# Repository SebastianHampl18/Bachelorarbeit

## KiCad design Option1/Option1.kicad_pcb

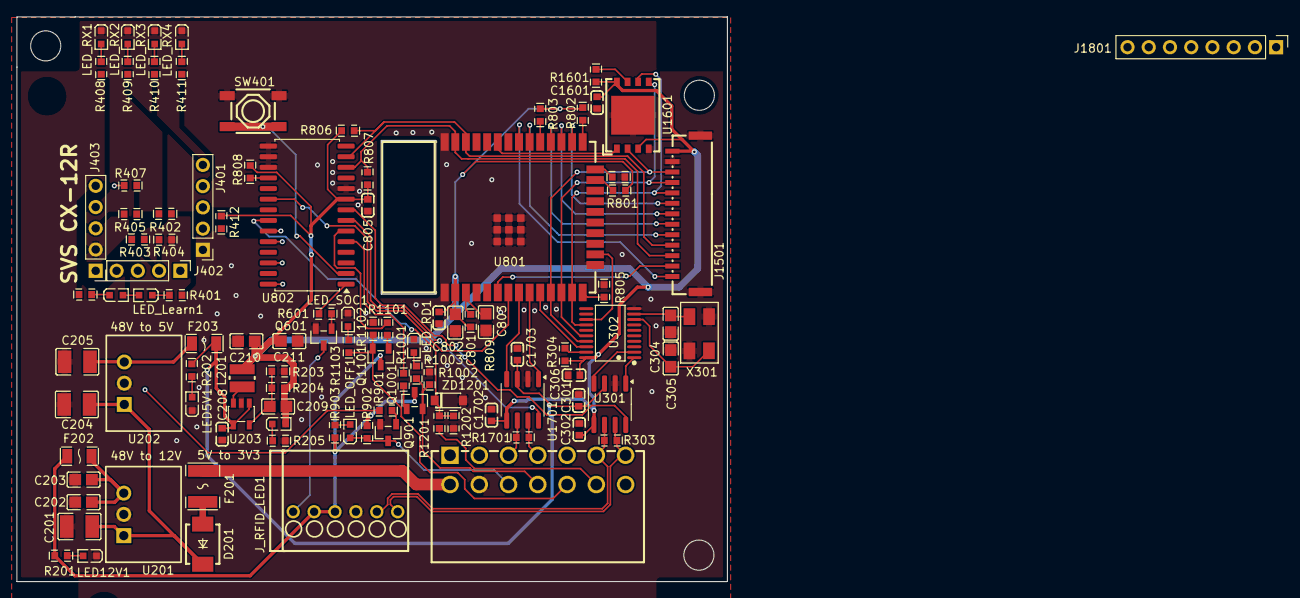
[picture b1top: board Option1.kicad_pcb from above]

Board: 2 copper layers, 85.0 x 67.5 mm, 104 parts (0 on the bottom side), 83 nets.

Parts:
C201, C204: 10uF / 63V; C1210
C202, C203: 10uF / 16V; C0805
C205: 22uF / 10V; C1210
C208: 22uF / 6.3V; C0603
C209, C304, C305: 22pF; C0805
C210, C211, C801: 22uF; C0805
C301, C302, C306, C802, C805, C1601, C1702, C1703: 100nF; C0603
C803: 10 uF; C0805
D201: SS310_C14281; SMB_L4.6-W3.6-LS5.3-R-RD
F201: JK-MSMD030-60V; F1812
F202: JK-NSMD075-13.2; F1206
F203: JK-NSMD075; F1206
J401, J403: Conn_01x05_Pin; PinHeader_1x05_P2.54mm_Vertical
J402: Conn_01x04_Pin; PinHeader_1x04_P2.54mm_Vertical
J503: KF2EDGKRG-3.5-2*7P; CONN-TH_14P-P3.50_KEFA_KF2EDGKRG-3.5-2X7P
J999: Phoenix_Connetor_07x2pin_toWire; Phonix_Connector_07x2pin_toWire
J1501: GH-13AB; CONN-SMD_GH-13AB
J1801: Conn_01x08_Socket; PinHeader_1x08_P2.54mm_Vertical
J_RFID_LED1: 1989780; CONN-TH_6P-P2.50_1989780
L201: 2.2uH; IND-SMD_L3.0-W3.0_NR3010
LED3V3: XL-1608SYGC-06; LED0603-RD_GREEN
LED5V1: XL-1608SYGC-5; LED0603-RD_GREEN
LED12V1: XL-1608SYGC-12; LED0603-RD_GREEN
LED_Error1: XL-1608SYGC-06; LED0603-RD_GREEN
LED_Learn1: XL-1608SYGC-06; LED0603-RD_GREEN
LED_OFF1: XL-1608SYGC-06; LED0603-RD_GREEN
LED_RD1: XL-1608SYGC-06; LED0603-RD_GREEN
LED_RX1, LED_RX2, LED_RX3, LED_RX4: XL-1608SYGC-06; LED0603-RD_GREEN
LED_SOC1: XL-1608SYGC-06; LED0603-RD_GREEN
Q601, Q901, Q1001, Q1101: JY2302; SOT-23-3_L2.9-W1.3-P0.95-LS2.4-BR
R201, R903, R1003, R1103: 1.8kΩ; R0603
R202: 560Ω; R0603
R203: 150k; R0603
R204: 680k; R0603
R205, R401, R406, R408, R409, R410, R411: 220Ω; R0603
R303, R1701: 120Ω; R0603
R304, R801, R802, R803, R804, R805, R808: 10kΩ; R0603
R402, R407: 10K; R0603
R403, R404, R405, R412, R809, R902, R1002, R1102, R1202, R1601: 10k; R0603
R601, R901, R1001, R1101: 1k; R0603
R806, R807: 4.7kΩ; R0603
R1201: 27k; R0603
SW401: 4*4*1.7; SW-SMD_4P-L5.2-W5.2-P3.70-LS6.5
U201: U7812-500; PWRM-TH_3P-L11.6-W9.0-P2.54
U202: U7805-500; PWRM-TH_3P-L11.6-W9.0-P2.54
U203: SY8089AAAC; SOT-23-5_L3.0-W1.7-P0.95-LS2.8-BR
U301, U1701: TJA1051T-3; SOIC-8_3.9x4.9mm_P1.27mm
U302: MCP2515-I/ST; TSSOP-20_L6.5-W4.4-P0.65-LS6.4-BL
U801: ESP32-WROOM-32E-N4; WIFI-SMD_ESP32-WROOM-32E-A
U802: MCP23017_SO; SOIC-28W_7.5x17.9mm_P1.27mm
U1601: W25Q512JVEIQ; WSON-8_L8.0-W6.0-P1.27-TL-EP
X301: XL1EL89CSI-111YLC-8M; CRYSTAL-SMD_4P-L5.0-W3.2-BL-7I12288F20UCG
ZD1201: BZT52C3V6_C2113; SOD-123_L2.8-W1.8-LS3.7-RD

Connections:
3.3V: C209.1, C210.1, C211.1, C302.1, C306.1, C801.1, C802.1, C805.1, C1601.2, C1702.1, J403.1, J1501.13, J1801.8, L201.2, LED3V3.2 (A), LED_Error1.2 (A), LED_Learn1.2 (A), R204.1, R304.2, R402.2, R403.2, R405.2, R407.2, R412.1, R801.1, R802.1, R803.1, R806.2, R807.2, R808.2, R809.1, R1601.2, U301.5 (VIO), U302.20 (VDD), U801.2 (3V3), U802.9 (VDD), U1601.3 (WP#(IO2), U1601.8 (VCC), U1701.5 (VIO)
5V: C208.1, C301.1, C1703.1, F203.2, R202.2, U203.1 (EN), U203.4 (IN), U301.3 (VCC), U1701.3 (VCC)
12V: F202.2, J_RFID_LED1.2, J_RFID_LED1.3, Q1001.3 (D), Q1101.3 (D), R201.2, R902.2, R903.2
48V: F201.1, J503.2
48V_Fused: C201.1, C204.1, D201.2 (K), U201.1 (Vin), U202.1 (Vin)
/CAN1 Tranciever/CAN_H: J503.7, R1701.2, U1701.7 (CANH)
/CAN1 Tranciever/CAN_L: J503.5, R1701.1, U1701.6 (CANL)
/CAN1 Tranciever/CAN_S-Mode: U802.7 (GPB6), U1701.8 (S)
/CAN2_Tranciever/CAN_H: J503.13, J_RFID_LED1.6, R303.2, U301.7 (CANH)
/CAN2_Tranciever/CAN_L: J503.11, J_RFID_LED1.5, R303.1, U301.6 (CANL)
/CAN2_Tranciever/CAN_RX: U301.4 (RXD), U302.2 (RXCAN)
/CAN2_Tranciever/CAN_S-Mode: U301.8 (S), U802.8 (GPB7)
/CAN2_Tranciever/CAN_TX: U301.1 (TXD), U302.1 (TXCAN)
/MCT Wlan/ESP_EN: C803.2, R809.2, U801.3 (EN)
/MCT Wlan/LED_On: R601.2, U802.1 (GPB0)
/MCT Wlan/LED_Signal: R1201.1, R1202.2, U802.22 (GPA1), ZD1201.1 (K)
/MCT Wlan/SPI_CS_RFID: J1801.1, U802.3 (GPB2)
/MCT Wlan/SPI_RST_RFID: J1801.7, U802.4 (GPB3)
/MCT Wlan/TX_2 (Remote Drive): R1001.2, U802.5 (GPB4)
/MCT Wlan/TX_3 (SOC): R1101.2, U802.6 (GPB5)
/Notaus Schalter/Notaus_VCU: J503.6, LED_OFF1.1 (K), Q901.3 (D), R902.1
/Powersupply/12V_OUT: C202.1, C203.1, F202.1, U201.3 (Vout)
/RemoteDrive Schalter/RemoteDrive_VCU: J503.8, Q1001.2 (S), R1002.2, R1003.2
/SOC Schalter/SOC_VCU: J503.10, Q1101.2 (S), R1102.2, R1103.2
/Stecker Input/VCU_LED: J503.12, R1201.2
/Stecker LED - RFID/Status_LED -: J_RFID_LED1.1, Q601.3 (D)
F2_Sel: J402.2, R403.1, R404.1
Fehler_LED: J403.5, R406.1, R407.1, U802.23 (GPA2)
GND: C201.2, C202.2, C203.2, C204.2, C205.2, C208.2, C210.2, C211.2, C301.2, C302.2, C304.1, C305.1, C306.2, C801.2, C802.2, C803.1, C805.2, C1601.1, C1702.2, C1703.2, J401.1, J403.2, J503.4, J1501.12, J1501.14, J1501.15, J1801.6, J_RFID_LED1.4, LED5V1.1 (K), LED12V1.1 (K), LED_RD1.1 (K), LED_RX1.1 (K), LED_RX2.1 (K), LED_RX3.1 (K), LED_RX4.1 (K), LED_SOC1.1 (K), Q601.2 (S), Q901.2 (S), R203.2, R205.2, R404.2, R804.2, R805.2, R1002.1, R1102.1, R1202.1, SW401.3, SW401.4, U201.2 (GND), U202.2 (GND), U203.2 (GND), U301.2 (GND), U302.10 (VSS), U801.1 (GND), U801.15 (GND), U801.38 (GND), U801.39 (GND), U802.10 (VSS), U802.15 (A0), U802.16 (A1), U802.17 (A2), U1601.4 (GND), U1601.9 (EP), U1701.2 (GND), X301.2 (GND), X301.4 (GND), ZD1201.2 (A)
IO0: R802.2, U801.25 (IO0)
IO2: R804.1, U801.24 (IO2)
IO4: J1501.8, U801.26 (IO4)
IO5: R803.2, U801.29 (IO5)
IO13: U302.13 (~INT), U801.16 (IO13)
IO14: J1501.9, J1801.2, U302.14 (SCK), U801.13 (IO14), U1601.6 (CLK)
IO16: J1501.7, U801.27 (IO16)
IO17: J1501.6, U801.28 (IO17)
IO18: J1501.5, U801.30 (IO18)
IO19: J1501.1, U801.31 (IO19)
IO21: U801.33 (IO21), U1601.1 (~CS)
IO22: J1501.4, R806.1, U801.36 (IO22), U802.13 (SDA)
IO23: J1501.3, R807.1, U801.37 (IO23), U802.12 (SCK)
IO25: U302.18 (~CS), U801.10 (IO25)
IO26: J1501.11, J1801.4, U302.17 (SO), U801.11 (IO26), U1601.2 (DO(IO1))
IO27: J1501.10, J1801.3, U302.16 (SI), U801.12 (IO27), U1601.5 (DI(IO0))
IO32: U801.8 (IO32), U1701.4 (RXD)
IO33: U801.9 (IO33), U1701.1 (TXD)
IO34: J1501.2, U801.6 (IO34)
IO35: U801.7 (IO35), U802.20 (INTA)
LED_Modus: J401.3, R401.1, R402.1, U802.21 (GPA0)
Lernmodus: J401.2, R412.2, SW401.1, SW401.2, U802.2 (GPB1)
MTD0: R801.2, U801.23 (IO15)
MTD1: R805.1, U801.14 (IO12)
unnamed: D201.1 (A), F201.2
unnamed: LED3V3.1 (K), R205.1
unnamed: LED5V1.2 (A), R202.1
unnamed: LED12V1.2 (A), R201.1
unnamed: LED_Error1.1 (K), R406.2
unnamed: LED_Learn1.1 (K), R401.2
unnamed: LED_OFF1.2 (A), R903.1
unnamed: LED_RD1.2 (A), R1003.1
unnamed: LED_RX1.2 (A), R408.2
unnamed: LED_RX2.2 (A), R409.2
unnamed: LED_RX3.2 (A), R410.2
unnamed: LED_RX4.2 (A), R411.2
unnamed: LED_SOC1.2 (A), R1103.1
unnamed: Q601.1 (G), R601.1
unnamed: Q901.1 (G), R901.1
unnamed: Q1001.1 (G), R1001.1
unnamed: Q1101.1 (G), R1101.1
unnamed: C205.1, F203.1, U202.3 (Vout)
unnamed: C209.2, R203.1, R204.2, U203.5 (FB)
unnamed: L201.1, U203.3 (LX)
unnamed: C304.2, U302.9 (OSC1), X301.3
unnamed: C305.2, U302.8 (OSC2), X301.1
unnamed: R304.1, U302.19 (~RESET)
unnamed: R808.1, U802.18 (~RESET)
unnamed: R1601.1, U1601.7 (~HOLD/RESET#(IO3))
RX_1: J402.4, R408.1, R901.2
RX_2: J402.3, R409.1, U802.24 (GPA3)
RX_3: J401.5, R410.1, U802.26 (GPA5)
RX_4: J401.4, R411.1, U802.28 (GPA7)
TX_Analog: J403.3, R405.1

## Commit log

2025-05-28 Stand mit annähernd fertigem Schaltplan, Flashen, SPIFlash, Display, MCT Beschaltung fehlen;Datenbläter, etc
2025-05-30 SPI Flash hinzugefügt, IN/Outputs vereinheitlicht, USB Flash Möglichkeit hinzugefügt, Display fehtl noch
2025-06-03 Added Export for Review 1
2025-06-13 USB auf 3V3 umgebaut
2025-06-19 Erste issues eingearbeitet
2025-06-19 Datenblätter für korrigierten SPI-Flash und CAN2 Controller Oszillator hinzugefügt
2025-06-19 Oszillator für CAN-Controller hinzugefügt, Abschlusswiderstände eingefügt
2025-06-19 Transitor getauscht, Pulldown Widerstände für Definierten LOW Pegel hinzugefügt
2025-06-19 Widerstandswerte des Spannungsteiler angepasst und korrigiert
2025-06-19 Zweite 3V3 Spannungsversorgung für Display hinzugefügt
2025-06-19 SPI Flash getauscht
2025-06-19 Pojekt und Backups
2025-06-19 Alte Stecker zum litzen verschrauben auf Platine vorgesehn, 14 Pin Stecker zum Stecken fehlt, RFID und LED abklären
2025-06-23 USB Schaltung angepasst, Transistoren korrigiert, Stecker ausgetauscht, Dioden hinzugefügt
2025-06-23 Layout für Powersupply, CAN und Stecker hinzugefügt
2025-06-25 MCT und SPI zu Layout hinzugefügt
2025-06-26 funkempfänger mit Beschaltung zu Layout hinzugefügt, SPI und I2C teilnehmer geroutet, Löcher hinzugefügt, Stecker platziert
2025-07-01 Layout komplett bis auf RFID Leiste und 3V3 Erzeugung Display
2025-07-01 3V3 für Display hinzugefügt und gelayoutet, Brücke zwischen Display und Std 3V3 hinzugefügt in Schaltplan und Platine
2025-07-15 GND polygon hinzugefügt, unverbundene Pads verknüpft, 0 Ohm Widerstand für Display Strohmversorgung hinzugefügt
2025-07-17 EasyEDA Lib in Projekt verschoben; Footprints, Silkscreen für designrule angepasst; Bauteilbeschriftungen entfernt, müssen neu angeordnet werden, JLC Rules eingebunden, Designrules erfolgreich bis au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
2025-07-22 Leiterbahndicke hinzugefügt, Via-Dicke angepasst, Bauteil referenzen hinzugefügt
2025-07-22 Stand 1 PCB Review
2025-07-28 Stecker nach hinten verschoben, Platine am vorderen Rand verlängert, Farbprints + Ref Feld hinzugefügt, Review eingearbeitet: Leiterbahnen dicker gemacht für Spannungsversorgung, Löcher verschoben, K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
2025-07-28 Step ohne Bauteile
2025-07-29 Dokument für Bachelorarbeit hinzugefügt und ersten Entwurf für Inhaltsverzeichnis erstellt
2025-07-29 Minimale Änderungen, Ausschnitt für USB Größer
2025-07-31 C++ Projekt begonnen mit PlatformIO in VS Code; headerdatei mit defines angelegt, init_ports funktion, funktionen als Prototypen angelegt
2025-07-31 LEDs für RX Ausgänge des Funkmodules hinzugefügt
2025-07-31 Datenblatt für GPIO Expander hinzugefügt
2025-08-02 interrupts angelegt
2025-08-03 Inhaltsverzeichnis angepasst
2025-08-04 Vorlage für Paarvergleich und Nutzwertanalyse erstellt
2025-08-06 Kapitel 4 - Konzepte begonnen mit Erklärung zu Paarvergleichen und Nutzwertanalysen
2025-08-06 Paarvergleich für Wifi begonnen, Kopitel 4.1 paarvergleiche algemeines vorgehen und system beschrieben
2025-08-08 Funktionen für Read/Write I2C hinzugefügt, test steht aus
2025-08-09 GPIO Expander Functionen für Write und read vollendet, begonnen Funktionen durch Read/Write I2C zu erweitern, wo sie benötigt werden
2025-08-12 Software fortgeschritten
2025-08-12 lib gespeicert
2025-08-13 Initialisierung ausgebaut auf Port Expansion
2025-08-14 Kabelseitigen Stecker für JLC Bestellung hinzugefügt. Footprint erstellt und 3D Modell hinzugefügt, Footprint/3DModell von 6Pin Stecker und Fuse korrigiert
2025-08-14 Added interrupt inits and interrupt service routines for GPIO Expansion
2025-08-15 Platine verkleinert, um besser in gehäuse zu passen, PullUp Widerstand an Button hinzugefügt
2025-08-15 Interrupt Service Routinen und Abarbeitung der ISR Flags in Main hinzugefügt. Nur Interrupts vom GPIO Expander, Keine Interrupt behandlung für CAN oder SPI
2025-08-17 LEDs an Transistoren hinzugefügt, Layout angepasst, LEDs eingefügt, LEDs zeigen an, ob Transsitor durchgeschalten ist
2025-08-17 Learn RF Controll Function erstelllt und begonnen
2025-08-18 Added handling for RF_Learning including RF ACK and Error handling
2025-08-18 learn rf angepasst, es werden keine schleifen mehr durchlaufen, es gibt kein delay, stattdessen über millis() gelöst
2025-08-19 Neue STEP Modelle erzeugt und exportiert
2025-08-19 Gerber Files, Production Files und weitere Fabrication Dateien für JLC PCB Bestellung erstellt
2025-08-19 Dateien für erste Bestellung gezippt, Pfad für verwendetes JLC Plugin hinzugefügt
2025-08-19 Library korrigiert auf Projekt Library. Footprints in Fabrication Files korrigiert. Neue Gerber files, BOM und Positionsdaten erstellt, Bestellung 1 Zip Datei entfernt
2025-08-19 BOM und Positionsdaten korrigiert
2025-08-19 Gerber und Fabrication Files feretig für bestellung, muss mit andreas reden. Alle Pinheader von Platine und Stüclkliste ausgeschlossen
2025-08-19 Reset SPI ohne delay() umgebaut; Datenblatt von RFID Reader hinzugefügt
2025-08-21 Programming Header hinzugefügt für flashen via DevKit
2025-08-26 Bestellung abgeschlossen. Aktueller Stand für Bestellung 1
2025-08-27 init_ca und process Can für CAN1 hinzugefügt
2025-08-28 INIT WIFI und webseiten hinzugefügt
2025-08-30 debugging ausgabe hinzugefügt, wifi html seiten hinzugefügt
2025-08-30 Funktionen für send und receive CAn Messages hinzugefügt, auswertung der CAN Messages fehlt;
    Send SOC und Remote Drive in main verschoben für zugriff auf CAn Objekt;
    Livedatenseite mti Java Skript hinzugefügt zur aktualisierung der Daten;
    Design für Livedaten, Root undEinstellungen festgelegt;
    ESP Storage initial values auf true gesetzt;
    Abfrage der im NVS gespeicherten Daten zur freischaltung der einzelnen funktionen durch erlauben des pollings im loop;
2025-08-30 dummy werte zur simulation von CAN veränderung um Webseite zu testen
2025-08-31 Display off hinzugefügt. Mehr einstellungsmöglichkeiten über Web interface, RF Controller anlernen per Netzwerk
2025-09-01 CAN1 decode und funktionen zur verarbeitung einzelner signale hinzugefügt, Structs für CAN-Signal und CAN-Messages erstellt und DBC Files nachgebildet
2025-09-01 DBC Files erstellt
2025-09-02 LED Blinken via CAN hinzugefügt, sowohl dauerhaft als auch mit definierter anzahl; Realisiert über Softwaretimer
2025-09-02 can2 init und isr für Can2 mit process can 2 hinzugefügt. SPI Register read und write hinzugefügt
2025-09-02 can2 dbc erstellt
2025-09-03 Beschreibund des aktuellen Systems und der Anforderungen begonnen
2025-09-04 Hertseller Einstellungen Webseite aufgebaut. Funktion zum Debugging der NvS hinzugefügt
2025-09-05 SOC Signal angelegt und zur Message PowerData hinzugefügt.
    Signal in Main definiert und hinzugefügt; CAN Schreibt direkt in global Variable für Webserver; Webserver für Herstellersettings angepasst, vollständig getestet und als SlideButton realisiert; Webser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
2025-09-05 IN dBC File SOC zu rx Signal für Option 1 hinzugefügt
2025-09-07 Anforderungen kapitel weiter geschrieben
2025-09-08 Solved some todos; CAN 2 init error handling; Added Librarys for Display
2025-09-08 Anforderungen kapitel fortgesetzt
2025-09-08 Anforderungen und Integration ions bestehende System übernommen
2025-09-09 Datenblätter für TouchController hinzugefügt, Library für Display eingebunden und hinzugefügt; InitDisplay begonnen - NACK Fehler bei I²C Communication
2025-09-10 Doku weitergeschrieben
2025-09-10 renamed touch controller to Dispaly controller
2025-09-11 Kapitel 3 fertig
2025-09-15 Erklärunge nchaltplan MCT und GPIO Exp fertig
2025-09-16 Schaltplan zu bachelorarbeit Dokument hinzuigefügt. Fertigf bis SPI Flash
2025-09-17 Kapitel über Schaltplan fortgesetzt, Fehler in Schaltplan korrigiert, DCDC getauscht, USB Schaltung angepasst, 3.3V Schaltung angepasst
2025-09-18 Platine korrigeiert, 5V DCDC getauscht, 3.3V Display Versorgung entfernt. Bauteile neu angeordnet, USB 5V auf 5V Supply geführt
2025-09-18 Notizen für PCB Design
2025-09-21 Kapitel 6 begonnen, Codeteile angepasst, GPIO Exp WriteBit korrigiert, Send SOC /RemoteDrive Delay entfernt
2025-09-21 Kapitel 6 Fortgesetzt, GPIO Exp, Funkmodul abgeschlossen, CAN1 begonnen.
2025-09-22 CAn1 Doku fertig, CAN 2 Init abgeschlossen
2025-09-22 CAN abgeschlossen , Wifi begonnen
2025-09-23 kap 6 abgeschlossen
2025-09-23 Kapitel 6 abgeschlossen, beschreibung von Nutzwertanalysen hinzugefügt, Paarvergleich für Wlan hinzugefügt, Konzeptbetrachtung für WiFi vorhanden, nicht in Doku eingearbeitet
2025-09-24 Kapitel 4 abgeschlossen
2025-09-25 Kapitel 2 bis auf Wifi fertig gestellt, Literaturverzeichnis begonnen
2025-09-26 Kapitel 2 abgeschlossen, Kapitel 1 und 8 fertig, Literatur fehlt für Kapitel 4, 5, 6, Kapitel 7 fehlt
2025-09-27 alle kapitel fertig, quellen fehlen
2025-09-28 init_interrupt Formatierung für Sreenshot angepasst
2025-09-28 Serielle Debuuging Ausgaben in Read_Register entfernt
2025-09-28 Kommentare angepasst
2025-09-28 Serielle Ausgaben in readBit für GPIO Expansion entfernt
2025-09-28 Auslassungen für GPIO_Expansion init hinzugefügt
2025-09-28 Beschreibung der Funktion send_remoteRequest entfernt
2025-09-28 Ko0mmentare im Loop für LED-Signal verkürzt
2025-09-28 learn_RFControl formatiert
2025-09-28 formatierung learn RF anmgepasst
2025-09-28 formatiert init_timer
2025-09-28 process CaN" FORMATIERT
2025-09-28 Formatierung handleEinstellungen
2025-09-28 Format handleSetrtings angeosst
2025-09-29 Formatierung vollständig abgeschlossen, Quellen fehlen
2025-09-29 Arbeit fertig woop woop
2025-09-29 Dokument zum Drucken und zur Abgabe per Email fertig und abgegeben
2025-10-20 Layout komplett neu überarbeitet, Neu Pinbelegung MCT, USB beschaltung muss noch korrigert werden
2025-10-22 Kleine Änderungen
2025-10-27 power Supply angepasst für 12V und 48V, Datenblätter für DCDCs hinzugefügt
2025-10-27 USB Beschaltung teilweise korrigiert, Fehlerbehebung steht aus
2025-10-29 Abschlusspräsentation hinzugefügt, Platinenform angepasst
2025-10-30 Fertigfe Abschlusspräsentation
